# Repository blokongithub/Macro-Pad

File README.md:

# Macro-Pad
My first electronics project

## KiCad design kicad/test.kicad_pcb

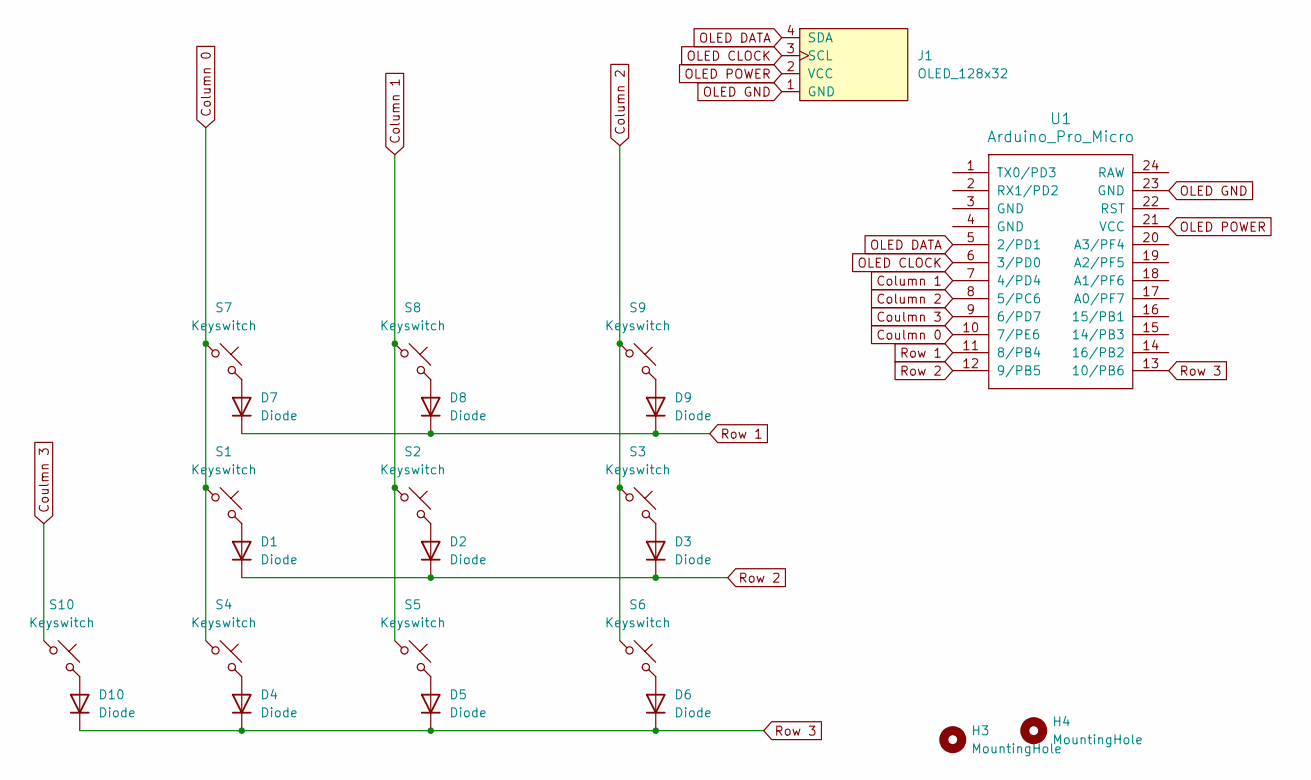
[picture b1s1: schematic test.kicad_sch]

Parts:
D1, D2, D3, D4, D5, D6, D7, D8, D9, D10: Diode; Diode_DO-35
H3, H4: MountingHole; MountingHole_3.2mm_M3
J1: OLED_128x32
S1, S2, S3, S4, S5, S6, S7, S8, S9, S10: Keyswitch; MX_PCB_1.00u
U1: Arduino_Pro_Micro

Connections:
Column 0: S1.1, S4.1, S7.1
Column 1: S2.1, S5.1, S8.1, U1.7 (4/PD4)
Column 2: S3.1, S6.1, S9.1, U1.8 (5/PC6)
Coulmn 0: U1.10 (7/PE6)
Coulmn 3: S10.1, U1.9 (6/PD7)
unnamed: D1.2 (A), S1.2
unnamed: D2.2 (A), S2.2
unnamed: D3.2 (A), S3.2
unnamed: D4.2 (A), S4.2
unnamed: D5.2 (A), S5.2
unnamed: D6.2 (A), S6.2
unnamed: D7.2 (A), S7.2
unnamed: D8.2 (A), S8.2
unnamed: D9.2 (A), S9.2
unnamed: D10.2 (A), S10.2
OLED DATA: J1.4 (SDA), U1.5 (2/PD1)
OLED CLOCK: J1.3 (SCL), U1.6 (3/PD0)
OLED GND: J1.1 (GND), U1.23 (GND)
OLED POWER: J1.2 (VCC), U1.21 (VCC)
Row 1: D7.1 (K), D8.1 (K), D9.1 (K), U1.11 (8/PB4)
Row 2: D1.1 (K), D2.1 (K), D3.1 (K), U1.12 (9/PB5)
Row 3: D4.1 (K), D5.1 (K), D6.1 (K), D10.1 (K), U1.13 (10/PB6)

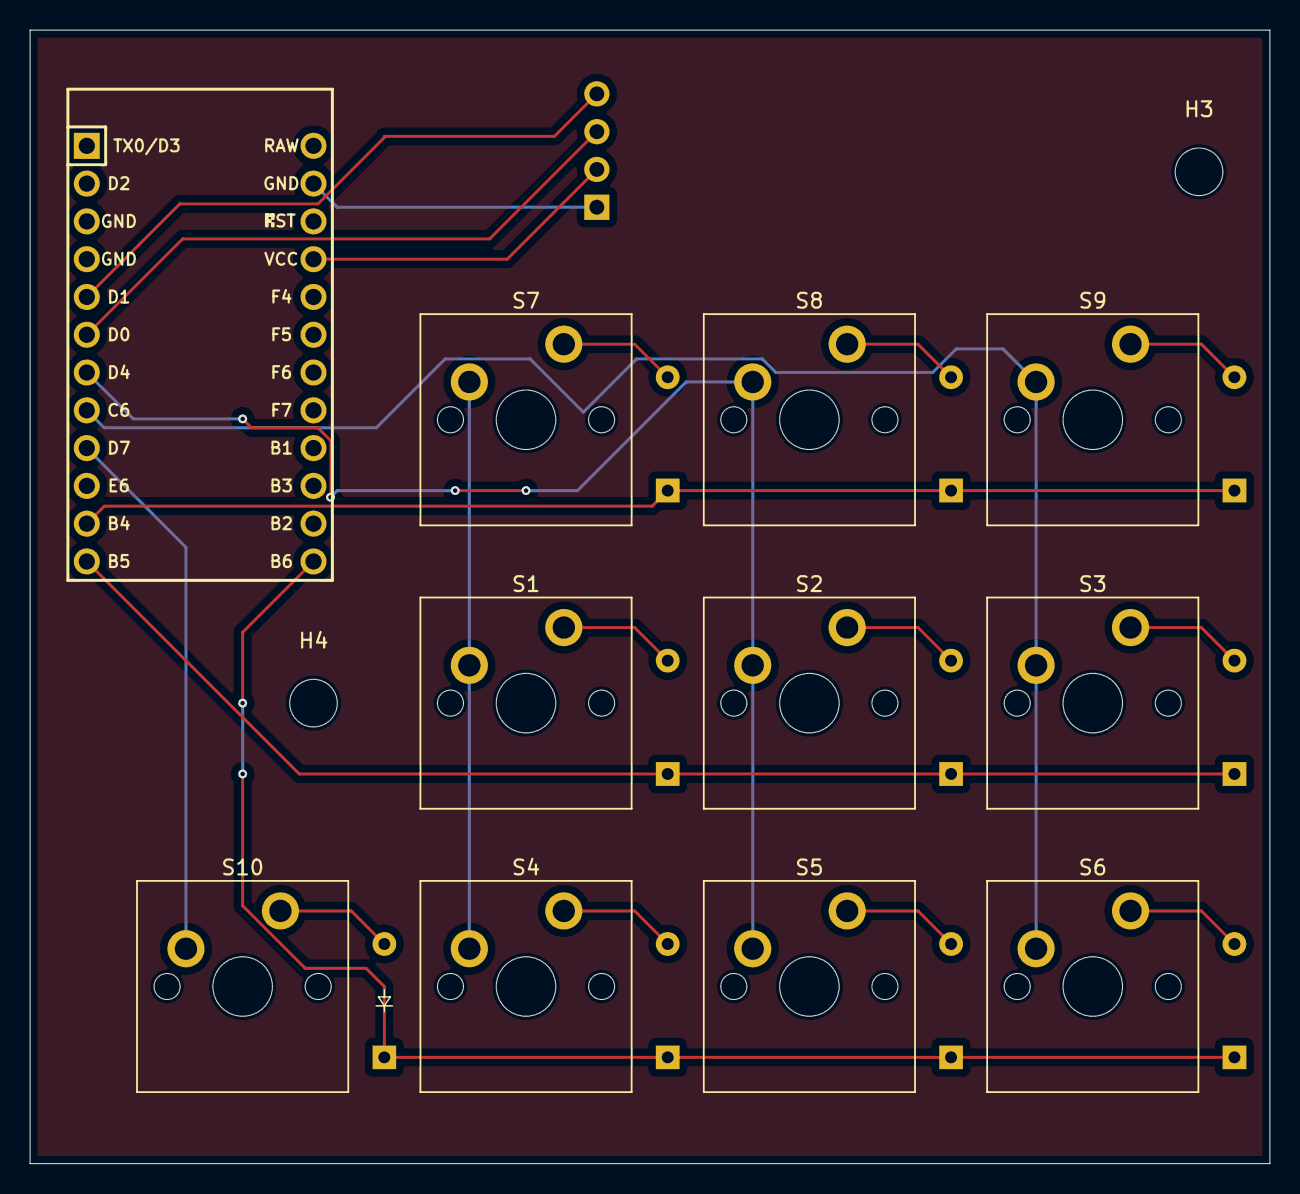
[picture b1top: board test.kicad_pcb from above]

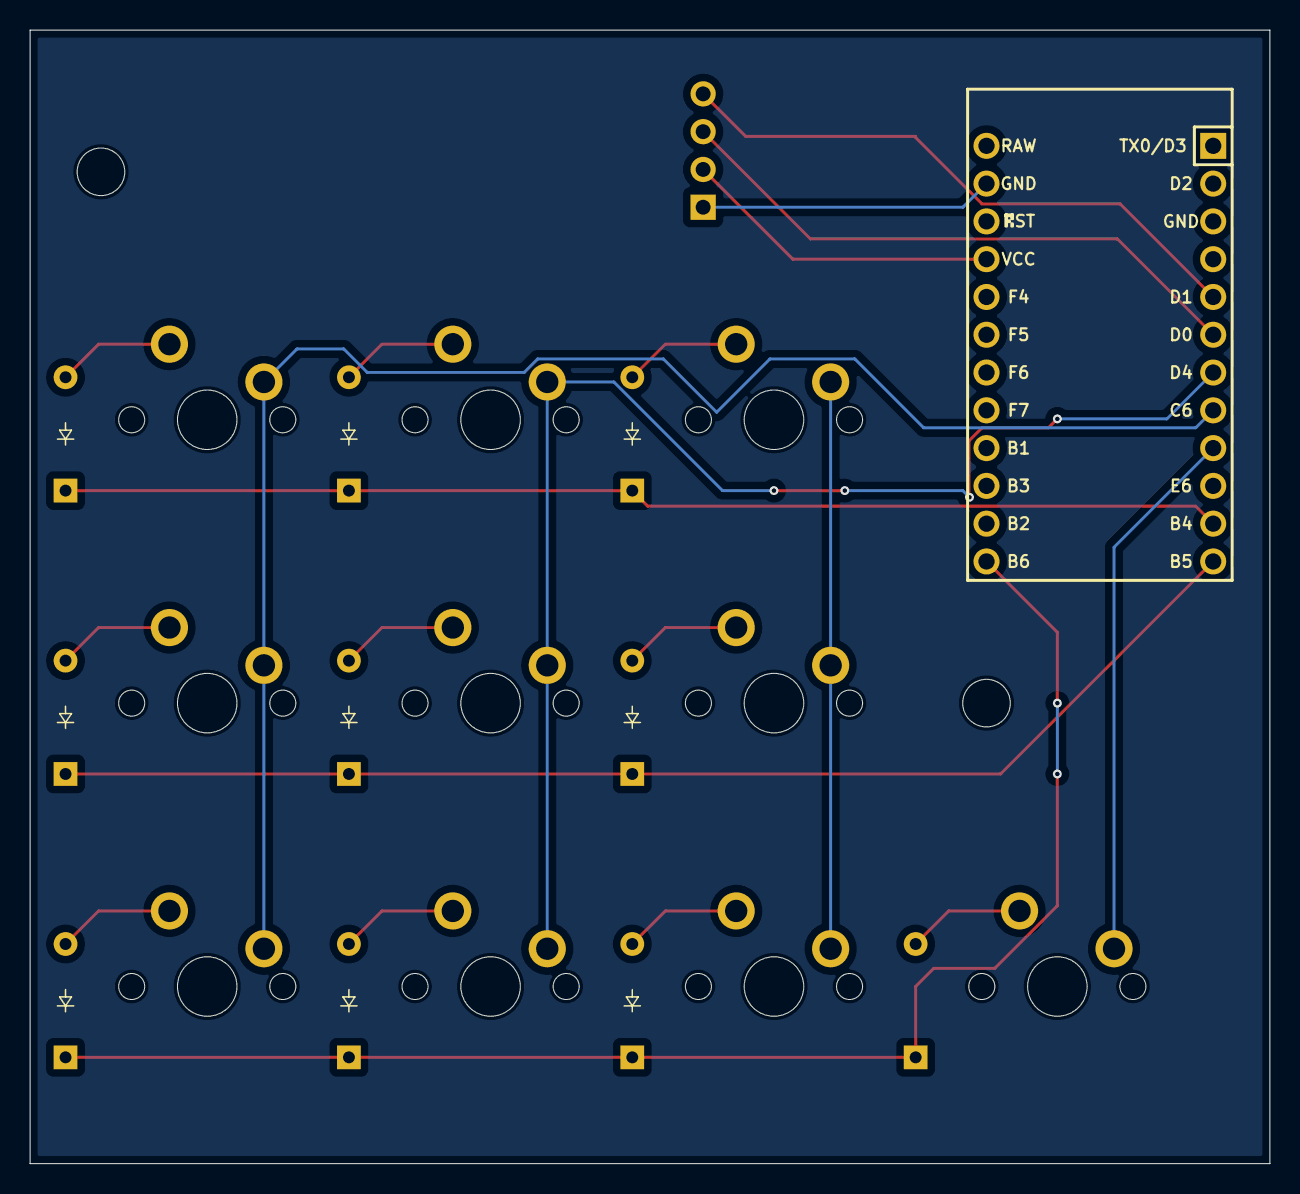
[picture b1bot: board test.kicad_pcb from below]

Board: 2 copper layers, 83.3 x 76.2 mm, 24 parts (9 on the bottom side), 21 nets.

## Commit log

2025-01-11 Rename image_2025-01-11_130309400.png to pcb.png
2025-01-11 Kicad
